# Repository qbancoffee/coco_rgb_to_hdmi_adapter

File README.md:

# coco_rgb_to_hdmi_adapter
RGB to HDMI adapter boards for the CoCo 1, the CoCo 2 and the CoCo 3.

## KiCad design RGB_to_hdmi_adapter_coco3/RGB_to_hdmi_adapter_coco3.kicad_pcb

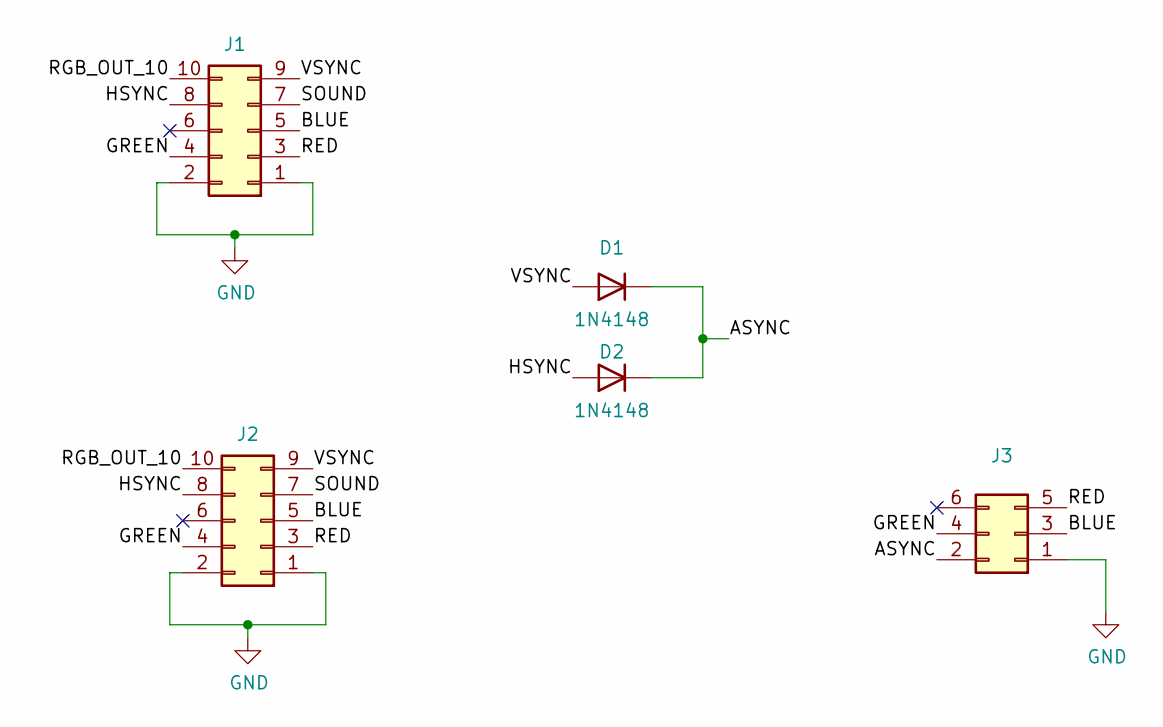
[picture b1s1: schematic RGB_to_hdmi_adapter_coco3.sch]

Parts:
D1, D2: 1N4148; D_DO-35_SOD27_P7.62mm_Horizontal; manufacturer part# 1N4148
J1: Conn_02x05_Odd_Even; IDC-Header_2x05_P2.54mm_Vertical; manufacturer part# PRPC005DAAN-RC
J2: Conn_02x05_Odd_Even; PinSocket_2x05_P2.54mm_Vertical; manufacturer part# PPPC052LFBN-RC
J3: Conn_02x03_Odd_Even; IDC-Header_2x03_P2.54mm_Vertical; manufacturer part# SBH11-NBPC-D03-ST-BK

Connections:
/ASYNC: D1.1 (K), D2.1 (K), J3.2
/BLUE: J1.5, J2.5, J3.3
/GREEN: J1.4, J2.4, J3.4
/HSYNC: D2.2 (A), J1.8, J2.8
/RED: J1.3, J2.3, J3.5
/RGB_OUT_10: J1.10, J2.10
/SOUND: J1.7, J2.7
/VSYNC: D1.2 (A), J1.9, J2.9
GND: J1.1, J1.2, J2.1, J2.2, J3.1

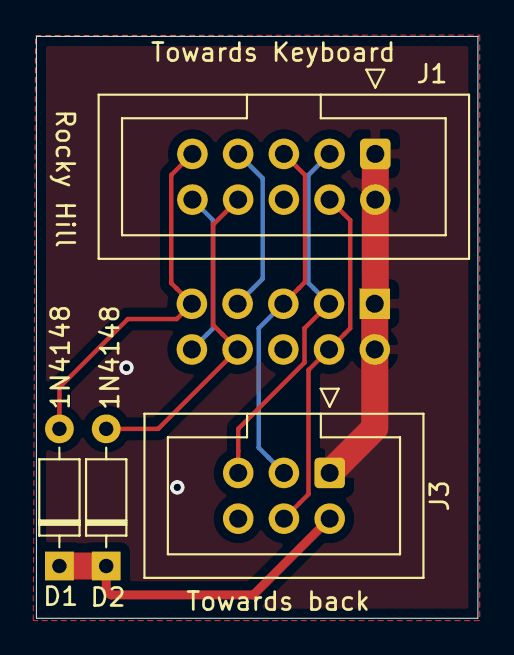
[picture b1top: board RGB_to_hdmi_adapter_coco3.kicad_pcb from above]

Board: 2 copper layers, 24.5 x 32.3 mm, 5 parts (1 on the bottom side), 9 nets.

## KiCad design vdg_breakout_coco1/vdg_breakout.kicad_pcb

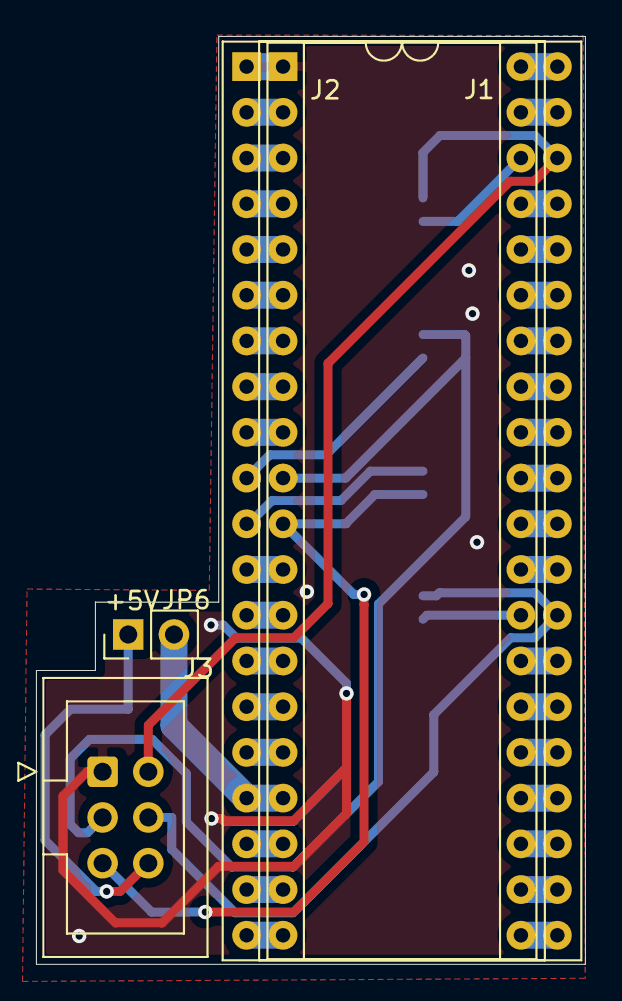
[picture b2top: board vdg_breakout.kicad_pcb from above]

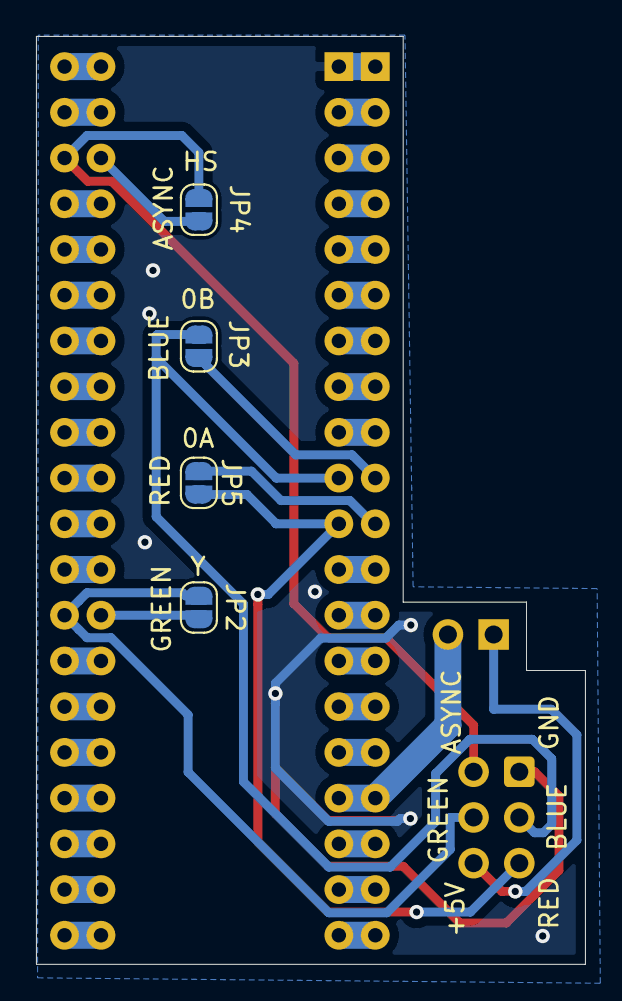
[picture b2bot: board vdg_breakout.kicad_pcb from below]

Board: 2 copper layers, 30.5 x 51.5 mm, 8 parts (4 on the bottom side), 45 nets.

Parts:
J1, J2: Conn_02x20_Counter_Clockwise; DIP-40_W15.24mm_Socket
J3: Conn_02x03_Odd_Even; IDC-Header_2x03_P2.54mm_Vertical
JP2, JP3, JP4, JP5: SolderJumper_2_Open; SolderJumper-2_P1.3mm_Open_RoundedPad1.0x1.5mm
JP6: Jumper_NO_Small; PinHeader_1x02_P2.54mm_Vertical

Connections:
+5V: J1.17, J2.17, JP6.2
/ASYNC: J1.38, J3.2, JP4.2
/BLUE: J1.10, J3.3, JP3.2
/CHB: J1.9, J2.9
/CLK: J1.33, J2.33
/CS: J1.39, J2.39
/DA0: J1.22, J2.22
/DA1: J1.23, J2.23
/DA2: J1.24, J2.24
/DA3: J1.25, J2.25
/DA4: J1.26, J2.26
/DA5: J1.13, J2.13
/DA6: J1.14, J2.14
/DA7: J1.15, J2.15
/DA8: J1.16, J2.16
/DA9: J1.18, J2.18
/DA10: J1.19, J2.19
/DA11: J1.20, J2.20
/DA12: J1.21, J2.21
/DD0: J1.3, J2.3
/DD1: J1.4, J2.4
/DD2: J1.5, J2.5
/DD3: J1.6, J2.6
/DD4: J1.7, J2.7
/DD5: J1.8, J2.8
/DD6: J1.2, J2.2
/DD7: J1.40, J2.40
/GM0: J1.30, J2.30
/GM1: J1.29, J2.29
/GM2: J1.27, J2.27
/GREEN: J1.28, J3.4, JP2.2
/HS: J2.38, JP4.1
/INV: J1.32, J2.32
/RED: J1.11, J3.5, JP5.2
/Y: J2.28, JP2.1
/~A~_G: J1.35, J2.35
/~A~_S: J1.34, J2.34
/~FS: J1.37, J2.37
/~INT~_~EXT: J1.31, J2.31
/~MS: J1.12, J2.12
/~RP: J1.36, J2.36
/ϴA: J2.11, JP5.1
/ϴB: J2.10, JP3.1
GND: J1.1, J2.1, J3.1
unnamed: J3.6, JP6.1
